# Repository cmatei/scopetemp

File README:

ScopeTemp
---------

An USB interface to temperature sensors mounted on the telescope, ST4
guider interface, PWM outputs for dew heater or fan control.

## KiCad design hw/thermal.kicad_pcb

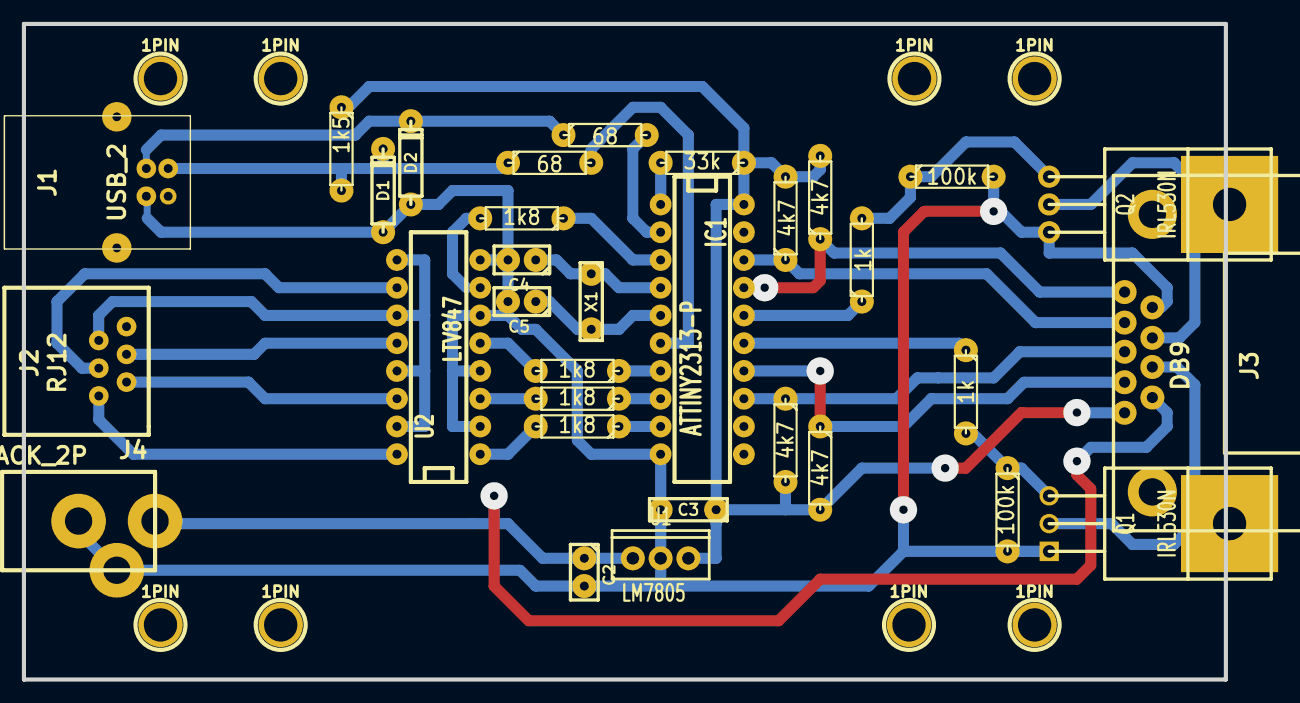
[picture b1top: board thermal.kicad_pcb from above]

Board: 2 copper layers, 110.0 x 60.0 mm, 40 parts (0 on the bottom side), 33 nets.

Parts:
1PIN, 1PIN#2, 1PIN#3, 1PIN#4, 1PIN#5, 1PIN#6, 1PIN#7, 1PIN#8: P***; 1pin
C2: 10u; C1
C3: 100n; C2
C4, C5: 22; C1
D1, D2: 3V6; D3
IC1: ATTINY2313-P; DIP-20__300_ELL
J1: USB_2; USB_B
J2: RJ12; RJ12_E
J3: DB9; DB9FC
J4: JACK_2P; pwrjack
Q1, Q2: IRL530N; TO220GDS
R1: 33k; R3
R2: 1k5; R3
R3, R4: 68; R3
R5, R6, R7, R8: 1k8; R3
R9, R10, R11, R12: 4k7; R3
R13, R14: 1k; R3
R15, R16: 100k; R3
U1: LM7805; LM78XXV
U2: LTV847; DIP-16__300
X1: 12MHz; C2

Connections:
+12V: C2.1, J3.9, U1.VI
/+DEC: J2.4, U2.10
/+RA: J2.3, U2.12
/-DEC: J2.5, U2.14
/-RA: J2.6, U2.16
/FAN1: IC1.15, R13.1
/FAN2: IC1.16, R14.1
/TEMP1: IC1.17, J3.1, R12.1
/TEMP2: IC1.18, J3.2, R11.1
/TEMP3: IC1.13, J3.3, R10.1
/TEMP4: IC1.14, J3.4, R9.1
GND: C2.2, C3.2, C4.2, C5.2, D1.1, D2.1, IC1.10, J1.4, J3.6, J4.2, Q1.S, Q2.S, R15.2, R16.2, U1.GND, U2.2, U2.4, U2.6, U2.8
unnamed: R5.2, U2.7
unnamed: R6.2, U2.5
unnamed: R8.2, U2.1
unnamed: IC1.1, R1.2
unnamed: D2.2, J1.3, R4.1
unnamed: J2.2, U2.9, U2.11, U2.13, U2.15
unnamed: R7.2, U2.3
unnamed: J3.7, Q2.D
unnamed: J3.8, Q1.D
unnamed: Q1.G, R13.2, R15.1
unnamed: Q2.G, R14.2, R16.1
unnamed: C4.1, IC1.4, X1.1
unnamed: IC1.9, R8.1
unnamed: IC1.8, R7.1
unnamed: IC1.7, R6.1
unnamed: IC1.6, R3.2
unnamed: C5.1, IC1.5, X1.2
unnamed: IC1.3, R5.1
unnamed: IC1.2, R4.2
unnamed: D1.2, J1.2, R2.2, R3.1
VCC: C3.1, IC1.20, J3.5, R1.1, R2.1, R9.2, R10.2, R11.2, R12.2, U1.VO

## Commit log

2014-09-07 Add README
2014-09-07 Cleanup hw dir
2014-09-07 V2 hardware schematics and pcb
2014-09-07 Update firmware to V2
2014-09-23 Add thermal.pdf
2014-09-24 Shuffle pins for the actual wiring changes
2014-09-24 Remove old software
2014-09-24 Rename schematic
2014-09-26 New INDI driver
